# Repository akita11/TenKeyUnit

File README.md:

# TenKey UNIT

GroveコネクタでM5Stack等の接続できる、数字の入力に便利なテンキーです。M5Stackの[CardKB Mini](https://www.switch-science.com/products/8445)と制御方法は互換ですので、CardKB Mini用のライブラリやUIFlowブロックを使用することができます。

## 使い方

M5Stack等のマイコンとGroveコネクタとをGroveケーブルで接続します。起動時にLEDが光ります（LEDつき版のみ）。キーを押すとそのキーのLEDがフラッシュします（LEDつき版のみ）。押したキーの情報(ASCIIコード)はGrove経由(I2C通信)で取得できます。

## 技術的詳細

### Grove経由の制御方法

通信方式はI2Cで、スレーブデバイス（I2Cアドレス=0x5f(7bit表記)）として動作します。マスタ側からI2C Readを行うと、直近で押したキーのASCIIコードを返します。

### 制御マイコン

制御マイコンはSTCmicro社のSTC8G08K-SOP16です。STCmicro社の書き込みツールをつかってファームウエアの書き換えを行うことができます。なおファームウエアのコンパイル方法や書き込み方法は、[STC8G_ProMini](https://www.switch-science.com/products/8216)のサポートページ等の情報を参照してください。

## 組立時の注意事項

プレート板（キースイッチ固定用）は表と裏があります。キースイッチがはまる穴が、基板上のキースイッチの位置にくる向きにしてください。またスペーサは2個重ねて（高さ3mmになります）ネジで固定します。

## Author

Junichi Akita (@akita11) / akita@ifdl.jp

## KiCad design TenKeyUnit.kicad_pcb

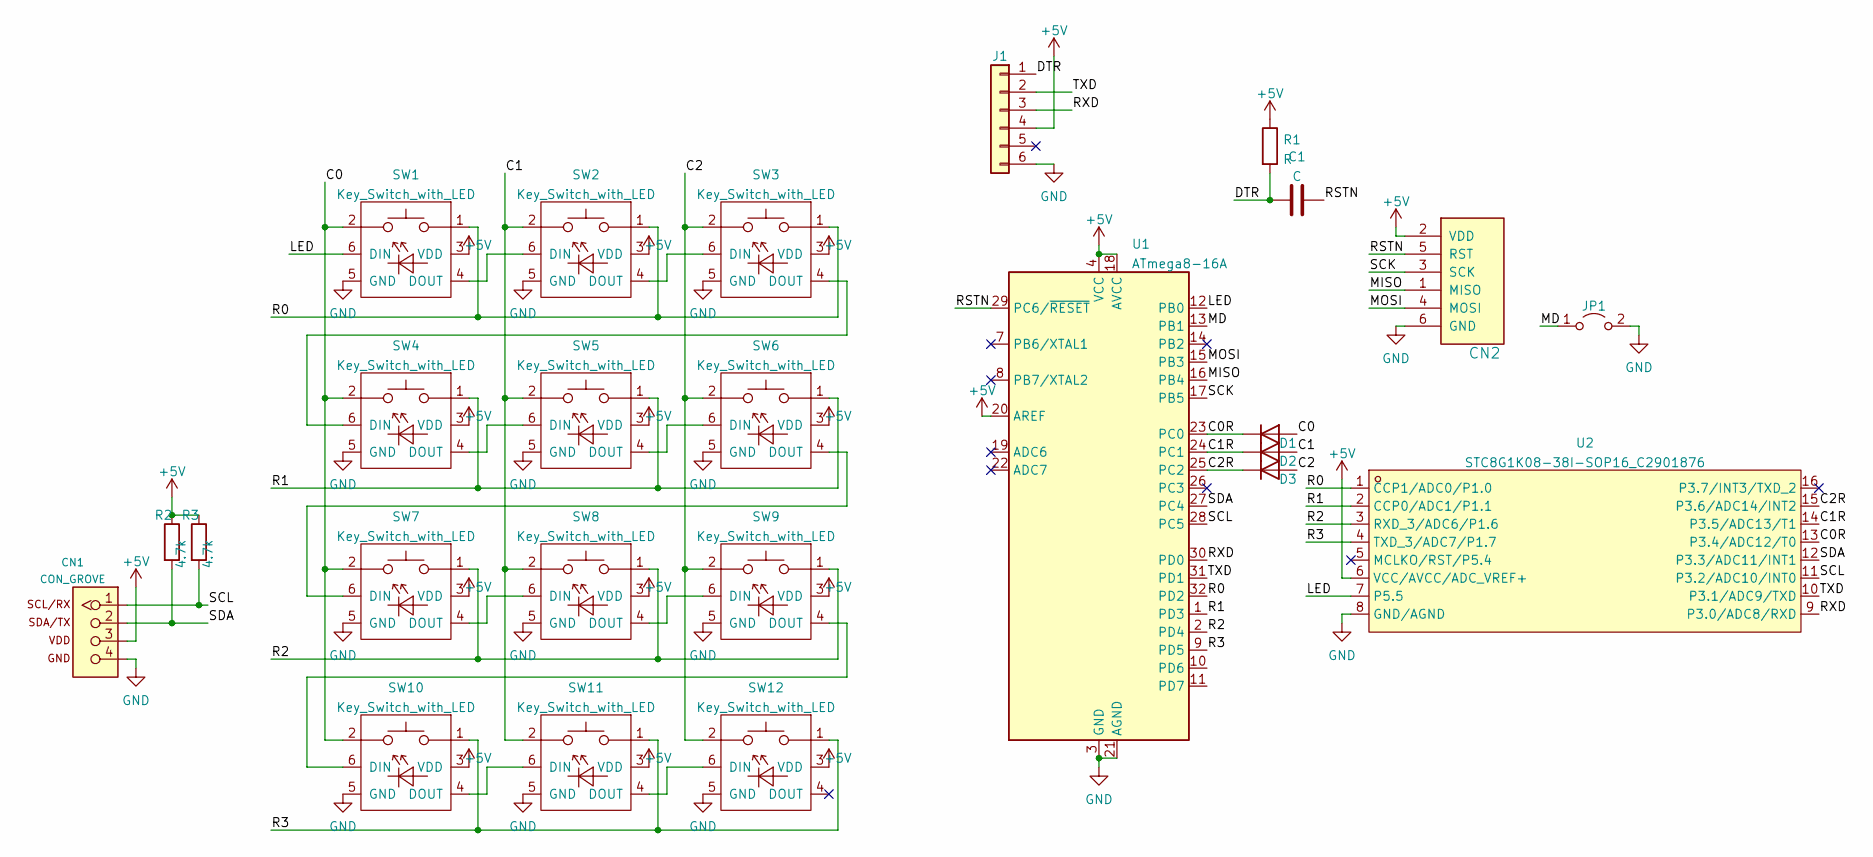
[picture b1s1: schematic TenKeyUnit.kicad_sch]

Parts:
C1: C; C_0603_1608Metric
CN1: CON_GROVE; CON_GROVE_H_roundPad
CN2: CON_AVRISP; PinHeader_2x03_P2.54mm_Vertical
D1, D2, D3: D; D_SOD-123F
J1: Conn_01x06; PinSocket_1x06_P2.54mm_Vertical
JP1: Jumper_2_Open; SolderJumper-2_P1.3mm_Open_Pad1.0x1.5mm
R1: R; R_0603_1608Metric
R2, R3: 4.7k; R_0603_1608Metric
SW1, SW2, SW3, SW4, SW5, SW6, SW7, SW8, SW9, SW10, SW11, SW12: Key_Switch_with_LED; MX_Socket_LED
U1: ATmega8-16A; TQFP-32_7x7mm_P0.8mm
U2: STC8G1K08-38I-SOP16_C2901876; SOP-16_L9.9-W3.9-P1.27-LS6.0-BL; LCSC Part C2901876

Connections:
+5V: CN1.3, CN2.2 (VDD), J1.4, R1.1, R2.1, R3.1, SW1.3 (VDD), SW2.3 (VDD), SW3.3 (VDD), SW4.3 (VDD), SW5.3 (VDD), SW6.3 (VDD), SW7.3 (VDD), SW8.3 (VDD), SW9.3 (VDD), SW10.3 (VDD), SW11.3 (VDD), SW12.3 (VDD), U1.4 (VCC), U1.6 (VCC), U1.18 (AVCC), U1.20 (AREF), U2.6 (VCC/AVCC/ADC_VREF+)
/C0: D1.2 (A), SW1.2, SW4.2, SW7.2, SW10.2
/C0R: D1.1 (K), U1.23 (PC0), U2.13 (P3.4/ADC12/T0)
/C1: D2.2 (A), SW2.2, SW5.2, SW8.2, SW11.2
/C1R: D2.1 (K), U1.24 (PC1), U2.14 (P3.5/ADC13/T1)
/C2: D3.2 (A), SW3.2, SW6.2, SW9.2, SW12.2
/C2R: D3.1 (K), U1.25 (PC2), U2.15 (P3.6/ADC14/INT2)
/DTR: C1.1, J1.1, R1.2
/LED: SW1.6 (DIN), U1.12 (PB0), U2.7 (P5.5)
/MD: JP1.1 (A), U1.13 (PB1)
/MISO: CN2.1 (MISO), U1.16 (PB4)
/MOSI: CN2.4 (MOSI), U1.15 (PB3)
/R0: SW1.1, SW2.1, SW3.1, U1.32 (PD2), U2.1 (CCP1/ADC0/P1.0)
/R1: SW4.1, SW5.1, SW6.1, U1.1 (PD3), U2.2 (CCP0/ADC1/P1.1)
/R2: SW7.1, SW8.1, SW9.1, U1.2 (PD4), U2.3 (RXD_3/ADC6/P1.6)
/R3: SW10.1, SW11.1, SW12.1, U1.9 (PD5), U2.4 (TXD_3/ADC7/P1.7)
/RSTN: C1.2, CN2.5 (RST), U1.29 (PC6/~RESET)
/RXD: J1.3, U1.30 (PD0), U2.9 (P3.0/ADC8/RXD)
/SCK: CN2.3 (SCK), U1.17 (PB5)
/SCL: CN1.1, R3.2, U1.28 (PC5), U2.11 (P3.2/ADC10/INT0)
/SDA: CN1.2, R2.2, U1.27 (PC4), U2.12 (P3.3/ADC11/INT1)
/TXD: J1.2, U1.31 (PD1), U2.10 (P3.1/ADC9/TXD)
GND: CN1.4, CN2.6 (GND), J1.6, JP1.2 (B), SW1.5 (GND), SW2.5 (GND), SW3.5 (GND), SW4.5 (GND), SW5.5 (GND), SW6.5 (GND), SW7.5 (GND), SW8.5 (GND), SW9.5 (GND), SW10.5 (GND), SW11.5 (GND), SW12.5 (GND), U1.3 (GND), U1.5 (GND), U1.21 (AGND), U2.8 (GND/AGND)
unnamed: SW1.4 (DOUT), SW2.6 (DIN)
unnamed: SW2.4 (DOUT), SW3.6 (DIN)
unnamed: SW3.4 (DOUT), SW4.6 (DIN)
unnamed: SW4.4 (DOUT), SW5.6 (DIN)
unnamed: SW5.4 (DOUT), SW6.6 (DIN)
unnamed: SW6.4 (DOUT), SW7.6 (DIN)
unnamed: SW7.4 (DOUT), SW8.6 (DIN)
unnamed: SW8.4 (DOUT), SW9.6 (DIN)
unnamed: SW10.4 (DOUT), SW11.6 (DIN)
unnamed: SW9.4 (DOUT), SW10.6 (DIN)
unnamed: SW11.4 (DOUT), SW12.6 (DIN)

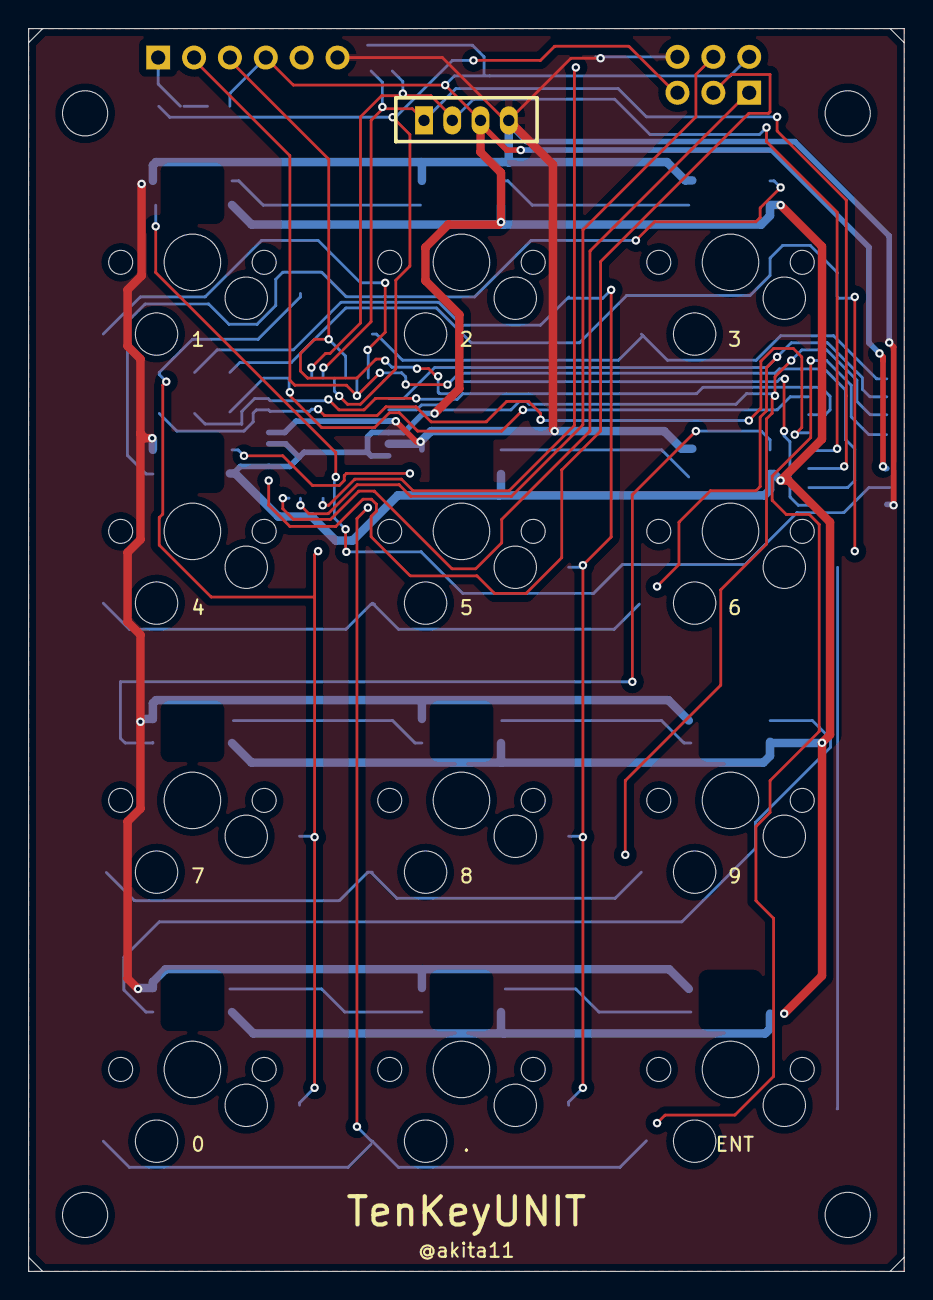
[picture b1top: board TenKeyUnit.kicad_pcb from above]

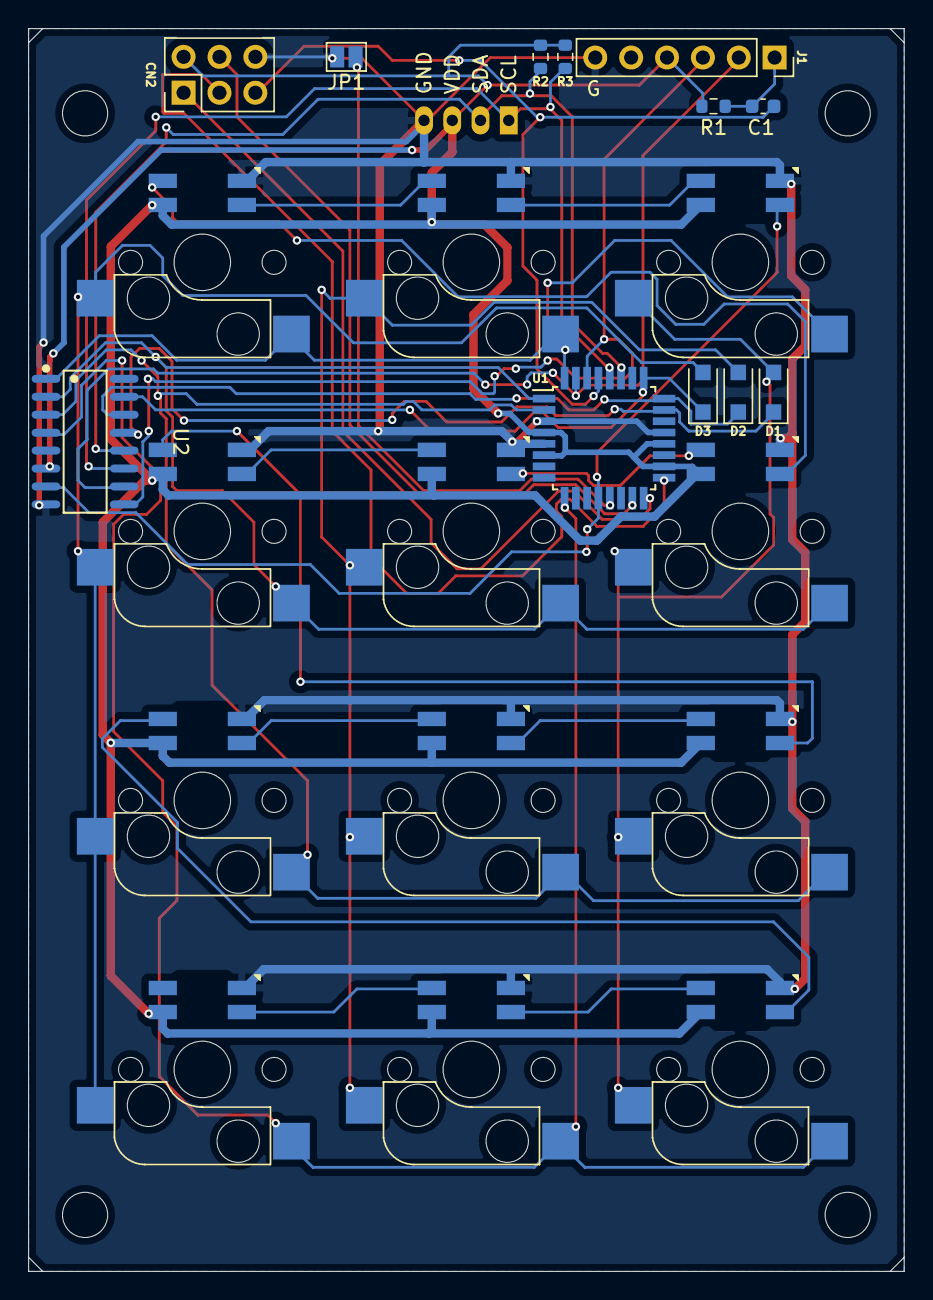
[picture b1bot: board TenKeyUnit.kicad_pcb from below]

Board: 2 copper layers, 62.0 x 88.0 mm, 25 parts (24 on the bottom side), 34 nets.
